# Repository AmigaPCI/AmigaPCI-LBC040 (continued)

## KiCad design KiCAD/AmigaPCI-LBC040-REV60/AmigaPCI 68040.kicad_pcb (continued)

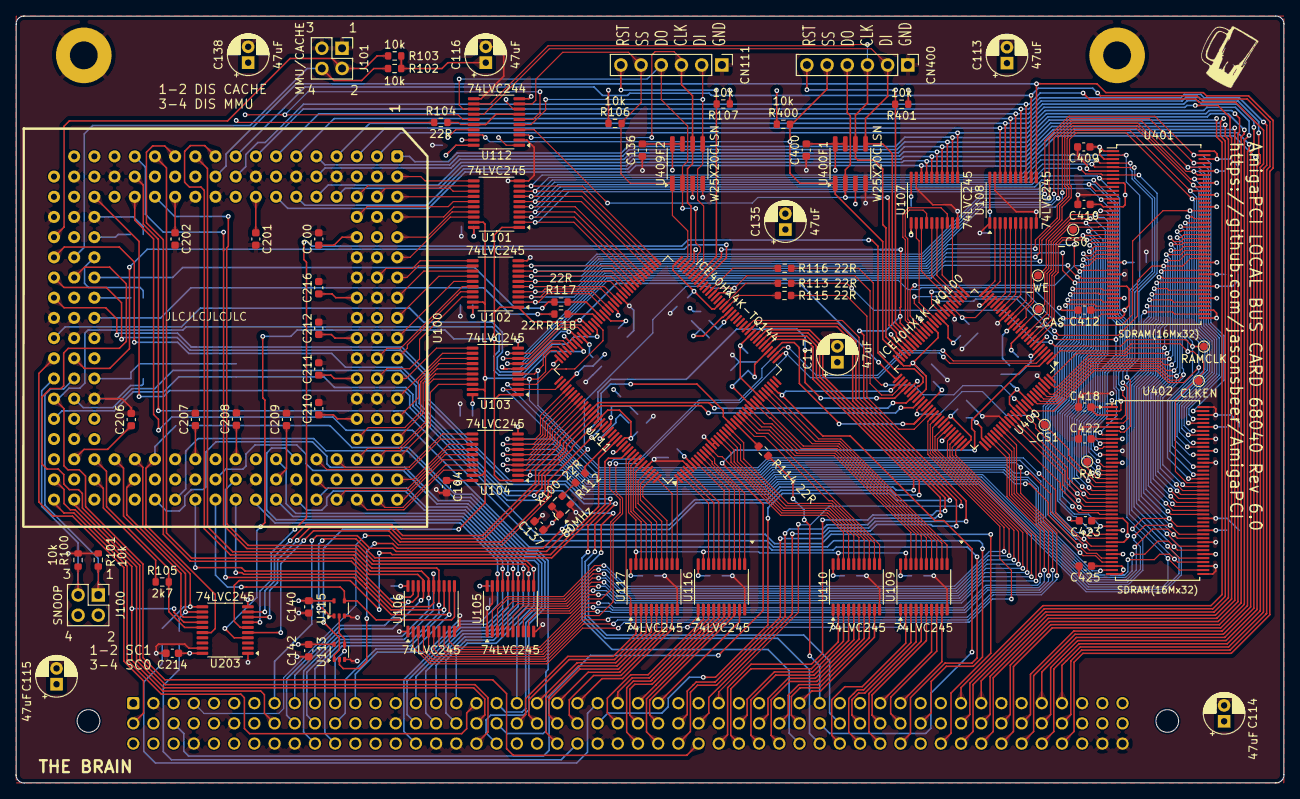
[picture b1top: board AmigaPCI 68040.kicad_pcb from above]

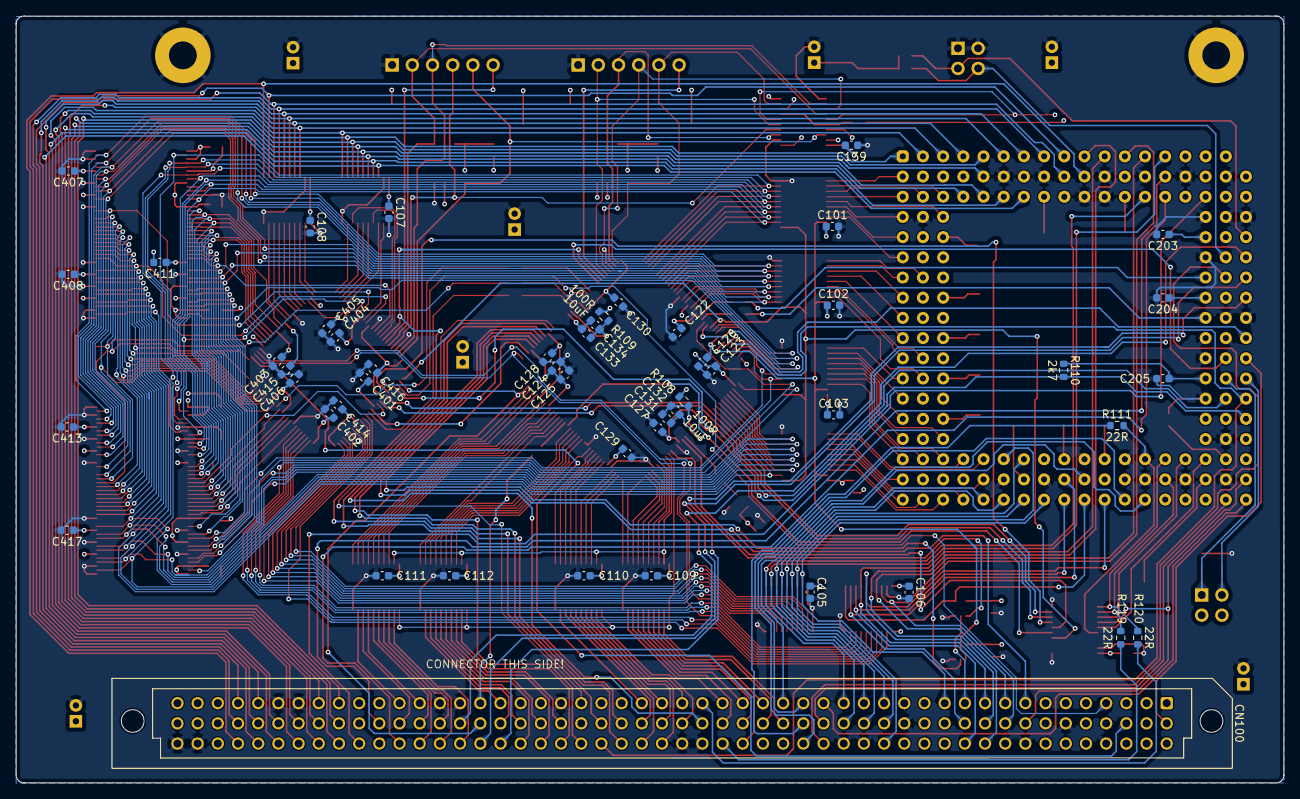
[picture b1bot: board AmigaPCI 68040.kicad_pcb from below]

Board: 6 copper layers, 159.5 x 96.5 mm, 135 parts (49 on the bottom side), 309 nets.

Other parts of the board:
C137, C216: 0.1uF; C_0603_1608Metric
R112: 22R; R_0603_1608Metric
U100: MC68040; PGA179
X100: 80MHz; Oscillator_SMD_ECS_2520MV-xxx-xx-4Pin_2.5x2.0mm

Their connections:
+3V3: C137.1, X100.1 (EN), X100.4 (V+); also elsewhere on the board
+5V: C216.1, U100.23 (Vcc), U100.27 (Vcc), U100.32 (Vcc), U100.38 (Vcc), U100.41 (Vcc), U100.44 (Vcc), U100.46 (Vcc), U100.48 (Vcc), U100.50 (Vcc), U100.53 (Vcc), U100.74 (Vcc), U100.77 (Vcc), U100.81 (Vcc), U100.82 (Vcc), U100.87 (Vcc), U100.88 (Vcc), U100.100 (Vcc), U100.104 (Vcc), U100.105 (Vcc), U100.107 (Vcc), U100.128 (Vcc), U100.131 (Vcc), U100.134 (Vcc), U100.138 (Vcc), U100.143 (Vcc), U100.152 (Vcc), U100.160 (Vcc); also elsewhere on the board
/CPU/SC0: U100.173 (SC0); also elsewhere on the board
/CPU/SC1: U100.156 (SC1); also elsewhere on the board
/CPU/_CDIS: U100.166 (_CDIS); also elsewhere on the board
/CPU/_MDIS: U100.150 (_MDIS); also elsewhere on the board
A0: U100.102 (A0); also elsewhere on the board
A1: U100.96 (A1); also elsewhere on the board
A2: U100.89 (A2); also elsewhere on the board
A3: U100.90 (A3); also elsewhere on the board
A4: U100.84 (A4); also elsewhere on the board
A5: U100.78 (A5); also elsewhere on the board
A6: U100.76 (A6); also elsewhere on the board
A7: U100.72 (A7); also elsewhere on the board
A8: U100.66 (A8); also elsewhere on the board
A9: U100.70 (A9); also elsewhere on the board
A10: U100.115 (A10); also elsewhere on the board
A11: U100.111 (A11); also elsewhere on the board
A12: U100.109 (A12); also elsewhere on the board
A13: U100.103 (A13); also elsewhere on the board
A14: U100.97 (A14); also elsewhere on the board
A15: U100.91 (A15); also elsewhere on the board
A16: U100.92 (A16); also elsewhere on the board
A17: U100.85 (A17); also elsewhere on the board
A18: U100.79 (A18); also elsewhere on the board
A19: U100.86 (A19); also elsewhere on the board
A20: U100.73 (A20); also elsewhere on the board
A21: U100.67 (A21); also elsewhere on the board
A22: U100.61 (A22); also elsewhere on the board
A23: U100.75 (A23); also elsewhere on the board
A24: U100.55 (A24); also elsewhere on the board
A25: U100.69 (A25); also elsewhere on the board
A26: U100.62 (A26); also elsewhere on the board
A27: U100.37 (A27); also elsewhere on the board
A28: U100.63 (A28); also elsewhere on the board
A29: U100.19 (A29); also elsewhere on the board
A30: U100.57 (A30); also elsewhere on the board
A31: U100.1 (A31); also elsewhere on the board
BCLKA: U100.133 (BCLK); also elsewhere on the board
CLKCPU: R112.1; also elsewhere on the board
D0: U100.39 (D0); also elsewhere on the board
D1: U100.21 (D1); also elsewhere on the board
D2: U100.40 (D2); also elsewhere on the board
D3: U100.2 (D3); also elsewhere on the board
D4: U100.3 (D4); also elsewhere on the board
D5: U100.4 (D5); also elsewhere on the board
D6: U100.5 (D6); also elsewhere on the board
D7: U100.6 (D7); also elsewhere on the board
D8: U100.25 (D8); also elsewhere on the board
D9: U100.7 (D9); also elsewhere on the board
D10: U100.8 (D10); also elsewhere on the board
D11: U100.9 (D11); also elsewhere on the board
D12: U100.10 (D12); also elsewhere on the board
D13: U100.11 (D13); also elsewhere on the board
D14: U100.12 (D14); also elsewhere on the board
D15: U100.13 (D15); also elsewhere on the board
D16: U100.29 (D16); also elsewhere on the board
D17: U100.14 (D17); also elsewhere on the board
D18: U100.30 (D18); also elsewhere on the board
D19: U100.15 (D19); also elsewhere on the board
D20: U100.16 (D20); also elsewhere on the board
D21: U100.17 (D21); also elsewhere on the board
D22: U100.34 (D22); also elsewhere on the board
D23: U100.51 (D23); also elsewhere on the board
D24: U100.18 (D24); also elsewhere on the board
D25: U100.52 (D25); also elsewhere on the board
D26: U100.36 (D26); also elsewhere on the board
D27: U100.58 (D27); also elsewhere on the board
D28: U100.54 (D28); also elsewhere on the board
D29: U100.64 (D29); also elsewhere on the board
D30: U100.65 (D30); also elsewhere on the board
D31: U100.60 (D31); also elsewhere on the board
GND: C137.2, C216.2, U100.20 (GND), U100.22 (GND), U100.24 (GND), U100.26 (GND), U100.28 (GND), U100.31 (GND), U100.33 (GND), U100.35 (GND), U100.42 (GND), U100.43 (GND), U100.45 (GND), U100.47 (GND), U100.49 (GND), U100.56 (GND), U100.59 (GND), U100.68 (GND), U100.71 (GND), U100.80 (GND), U100.83 (GND), U100.93 (GND), U100.94 (GND), U100.98 (GND), U100.99 (GND), U100.101 (GND), U100.106 (GND), U100.110 (GND), U100.113 (GND), U100.122 (GND), U100.125 (GND), U100.130 (GND), U100.132 (GND), U100.136 (GND), U100.137 (GND), U100.139 (GND), U100.146 (GND), U100.148 (TCK), U100.153 (GND), U100.154 (GND), U100.159 (GND), U100.161 (GND), U100.165 (GND), U100.170 (DLE), X100.2 (GND); also elsewhere on the board
unnamed: R112.2, X100.3 (OUT)
PCLK: U100.135 (PCLK); also elsewhere on the board
R_W-CPU: U100.112 (R_W); also elsewhere on the board
SIZ0: U100.119 (SIZ0); also elsewhere on the board
SIZ1: U100.118 (SIZ1); also elsewhere on the board
TM0: U100.114 (TM0); also elsewhere on the board
TM1: U100.108 (TM1); also elsewhere on the board
TM2: U100.95 (TM2); also elsewhere on the board
TT0: U100.117 (TT0); also elsewhere on the board
TT1: U100.116 (TT1); also elsewhere on the board
_AUTOVECTOR: U100.172 (_AVEC); also elsewhere on the board
_BB: U100.178 (_BB); also elsewhere on the board
_BG: U100.174 (_BG); also elsewhere on the board
_BR: U100.179 (_BR); also elsewhere on the board
_CPURST: U100.151 (_RSTI); also elsewhere on the board
_IPL0: U100.169 (_IPL0); also elsewhere on the board
_IPL1: U100.168 (_IPL1); also elsewhere on the board
_IPL2: U100.167 (_IPL2); also elsewhere on the board
_LOCK: U100.162 (_LOCK); also elsewhere on the board
_MI: U100.124 (_MI); also elsewhere on the board
_RSTOUT: U100.129 (_RSTO); also elsewhere on the board
_TA-CPU: U100.175 (_TA); also elsewhere on the board
_TBI-CPU: U100.155 (_TBI); also elsewhere on the board
_TCI-CPU: U100.171 (_TCI); also elsewhere on the board
_TEA-CPU: U100.157 (_TEA); also elsewhere on the board
_TS-CPU: U100.142 (_TS); also elsewhere on the board

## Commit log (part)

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2026-02-13 U111 daily. 12-FEB-2026
    Fix assertion of _TS on the CPU side of the FPGA during DMA cycles.
2026-02-14 U111 Daily. 14-FEB-2026
    Fixed issue where CPU starts a cycle on the same edge _BG is negated by the arbiter.
2026-02-26 U111 daily. 25-FEB-2026
    Fixed _TS assertion glitch during bus handoff.
2026-04-07 U111 verilog for Rev 6.0 LBC
    Includes changes for new routing.
2026-04-08 U400 Verilog for Rev 6.0 LBC
2026-04-15 AmigaPCI Local Bus Card Revision 6.0
2026-04-17 Revision 6.0 Gerber
2026-04-22 Add JLCPCB part numbers to KiCAD schematic.
2026-04-23 Change JLCPCB part number for 80MHz oscillator.
2026-04-26 Update 2x2 Pin Header Part Numbers
2026-04-26 Add BOM and P&P Files
2026-04-26 Add part number for DIN41612 connector.
2026-05-31 New RAM state machine and cache settings.
    Both these new U111 and U400 must be installed.
2026-06-20 U111 New Hardware Update
2026-06-22 U400 New Hardware Release Verilog
2026-06-23 Push hardware revision 6.0
